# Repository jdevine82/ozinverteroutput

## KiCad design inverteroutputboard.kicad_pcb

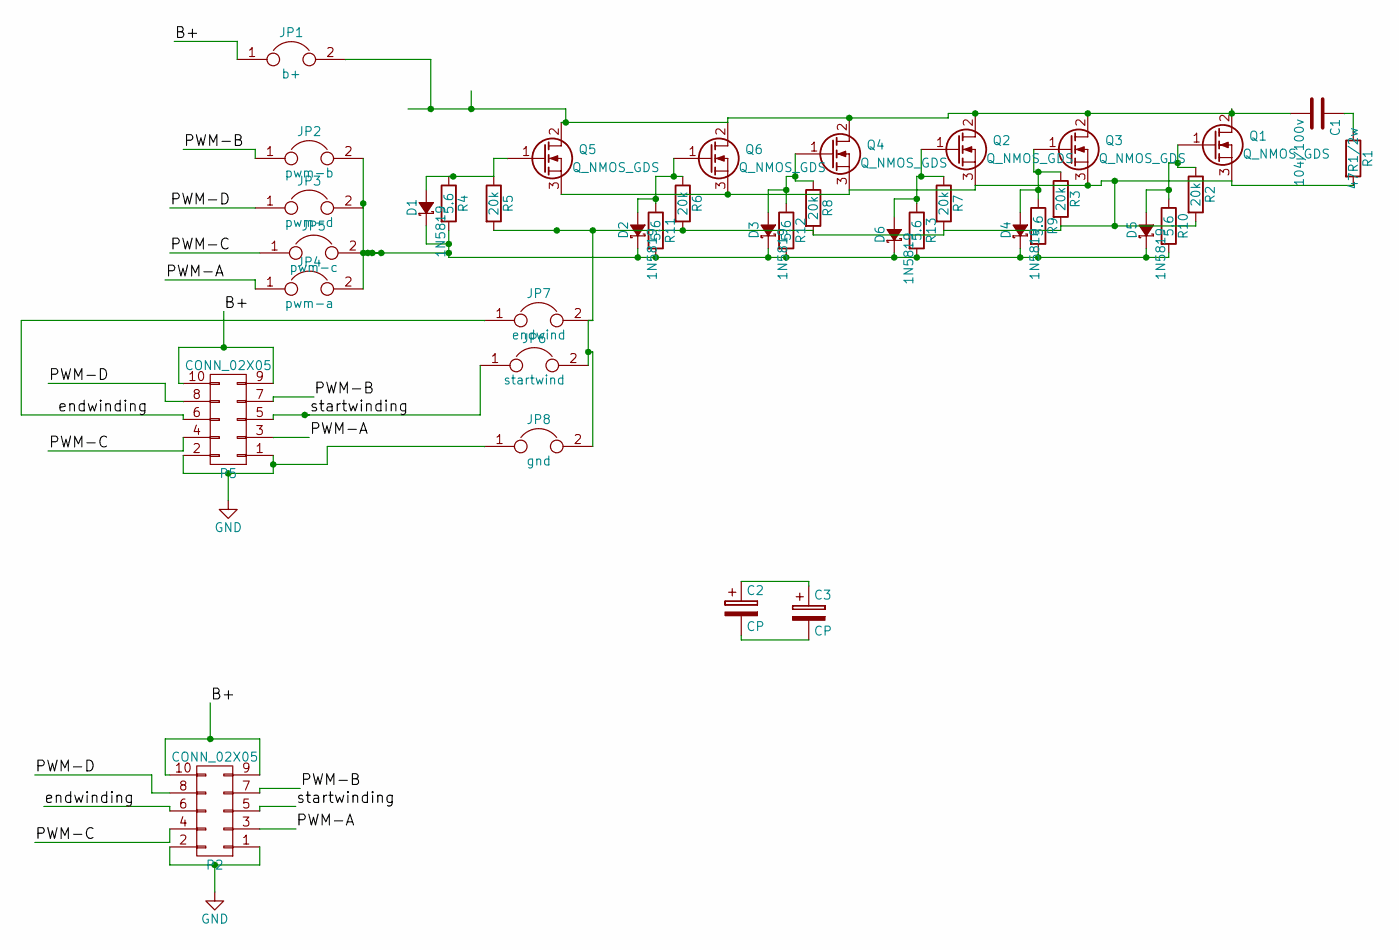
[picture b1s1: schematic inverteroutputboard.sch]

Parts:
C1: 104/100v; C_Disc_D7.5_P5
C2, C3: CP; C_Radial_D35_L51_P10
D1, D2, D3, D4, D5, D6: 1N5819; DO-214AB_Handsoldering
JP1: b+; JST_EH_B02B-EH-A_02x2.50mm_Straight
JP2: pwm-b; JST_EH_B02B-EH-A_02x2.50mm_Straight
JP3: pwm-d; JST_EH_B02B-EH-A_02x2.50mm_Straight
JP4: pwm-a; JST_EH_B02B-EH-A_02x2.50mm_Straight
JP5: pwm-c; JST_EH_B02B-EH-A_02x2.50mm_Straight
JP6: startwind; JST_EH_B02B-EH-A_02x2.50mm_Straight
JP7: endwind; JST_EH_B02B-EH-A_02x2.50mm_Straight
JP8: gnd; JST_EH_B02B-EH-A_02x2.50mm_Straight
P2, P5: CONN_02X05; IDC_Header_Straight_10pins
Q1, Q2, Q3, Q4, Q5, Q6: Q_NMOS_GDS; TO-220_Neutral123_Vertical
R1: 47R1/2w; Resistor_Horizontal_RM10mm
R2, R3, R5, R6, R7, R8: 20k; R_0603_HandSoldering
R4, R9, R10, R11, R12, R13: 5.6; R_0603_HandSoldering

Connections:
/B+: JP1.1, P2.9, P2.10, P5.9, P5.10
/PWM-A: JP4.1, P2.3, P5.3
/PWM-B: JP2.1, P2.7, P5.7
/PWM-C: JP5.1, P2.4, P5.4
/PWM-D: JP3.1, P2.8, P5.8
/endwinding: JP7.1, P2.6, P5.6
/startwinding: JP6.1, P2.5, P5.5
GND: JP8.1, P2.1, P2.2, P5.1, P5.2
unnamed: C1.1, R1.1
unnamed: C1.2, JP1.2, Q1.2 (D), Q2.2 (D), Q3.2 (D), Q4.2 (D), Q5.2 (D), Q6.2 (D)
unnamed: C2.1, C3.1
unnamed: C2.2, C3.2
unnamed: D1.1 (K), D2.1 (K), D3.1 (K), D4.1 (K), D5.1 (K), D6.1 (K), JP2.2, JP3.2, JP4.2, JP5.2, R4.2, R9.2, R10.2, R11.2, R12.2, R13.2
unnamed: D1.2 (A), Q5.1 (G), R4.1, R5.1
unnamed: D2.2 (A), Q6.1 (G), R6.1, R11.1
unnamed: D3.2 (A), Q4.1 (G), R8.1, R12.1
unnamed: D4.2 (A), Q3.1 (G), R3.1, R9.1
unnamed: D5.2 (A), Q1.1 (G), R2.1, R10.1
unnamed: D6.2 (A), Q2.1 (G), R7.1, R13.1
unnamed: JP6.2, JP7.2, JP8.2, Q1.3 (S), Q2.3 (S), Q3.3 (S), Q4.3 (S), Q5.3 (S), Q6.3 (S), R1.2, R2.2, R3.2, R5.2, R6.2, R7.2, R8.2

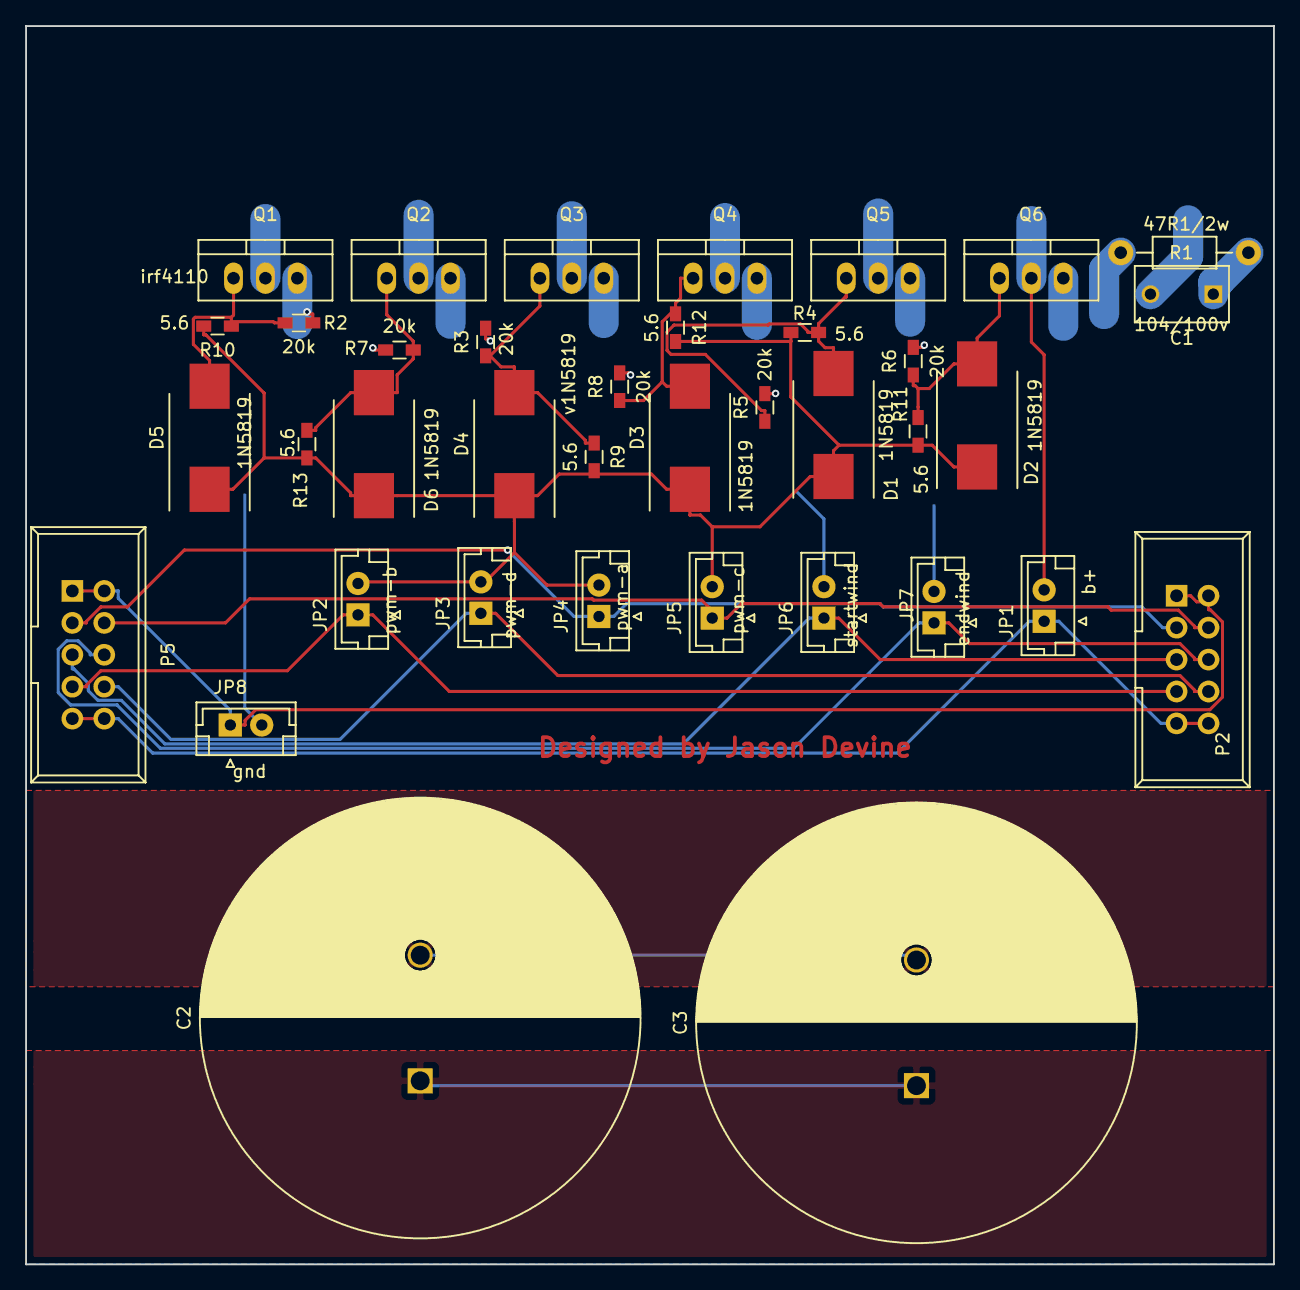
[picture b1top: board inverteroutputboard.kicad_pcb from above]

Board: 2 copper layers, 99.3 x 98.6 mm, 38 parts (0 on the bottom side), 20 nets.

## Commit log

2016-10-15 first draft layout -incomplete' '
2016-10-16 added jumbpers
2016-10-16 version 0.9 caps and connectors
2017-08-08 reworked plugs to make compatible with powerstar inverters and added better solder masking.
2017-08-08 removed old pdfs
